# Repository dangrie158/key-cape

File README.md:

# KeyCape

a simple UI extension for your PC / Mac. 

KeyCape offers the following Hardware I/Os:

* Cherry MX Switch with LED
* Encoder with Button
* 4 general purpose LEDs

As the firmware is still in development I'm not sure yet how to implement all I/O in a good way. Probably a HID Keyboard with the Cherry Switch acting as a ESC button (so vim is usable again for the new Mac Books with touchbar) and the encoder as vol up/down.

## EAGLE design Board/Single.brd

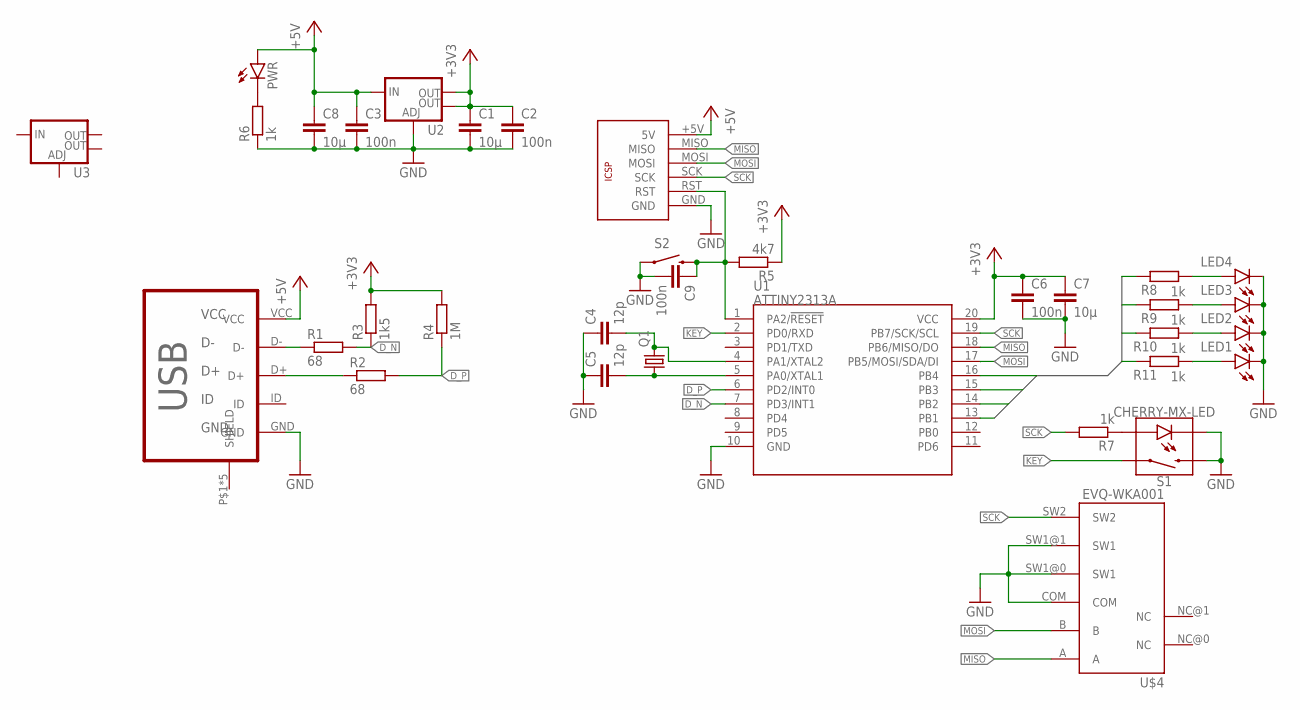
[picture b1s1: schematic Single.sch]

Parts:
C1, C7, C8: 10µ; C0603
C2, C3, C6, C9: 100n; C0603
C4, C5: 12p; C0603
LED1, LED2, LED3, LED4: LED0603; LED-0603
PWR: LED0603; LED-0603
Q1: CRYSTALCTS406; CTS406
R1, R2: 68; R0603
R3: 1k5; R0603
R4: 1M; R0603
R5: 4k7; R0603
R6, R7, R8, R9, R10, R11: 1k; R0603
S1: CHERRY-MX-LED
S2: SWITCH-MOMENTARY-2SMD-1101NE; TACTILE-SWITCH-1101NE
U1: ATTINY2313A; SOP20W
U2, U3: V_REG_LM1117SOT223; SOT223
U$1: ICSPTHROUGHHOLE; ICSP-THROUGHHOLE
U$2: MICRO-USB-B; MICRO_USB_4_LEGS
U$4: EVQ-WKA001

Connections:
+3V3: C1.1, C2.1, C6.1, C7.1, R3.2, R4.2, R5.1, U1.20 (VCC), U2.2 (OUT), U2.4 (OUT)
+5V: C3.1, C8.1, PWR.A, U2.3 (IN), U$1.+5V (5V), U$2.VCC
DUSB_N: R1.1, U$2.D-
DUSB_P: R2.1, U$2.D+
D_N: R1.2, R3.1, U1.7 (PD3/INT1)
D_P: R2.2, R4.1, U1.6 (PD2/INT0)
GND: C1.2, C2.2, C3.2, C4.1, C5.1, C6.2, C7.2, C8.2, C9.2, LED1.C, LED2.C, LED3.C, LED4.C, R6.1, S1.K (C), S1.S2, S2.1, U1.10 (GND), U2.1 (ADJ), U$1.GND, U$2.GND, U$4.COM, U$4.SW1@0 (SW1), U$4.SW1@1 (SW1)
KEY: S1.S1, U1.2 (PD0/RXD)
LED1: R11.2, U1.13 (PB1)
LED2: R10.2, U1.14 (PB2)
LED3: R9.2, U1.15 (PB3)
LED4: R8.2, U1.16 (PB4)
MISO: U1.18 (PB6/MISO/DO), U$1.MISO, U$4.A
MOSI: U1.17 (PB5/MOSI/SDA/DI), U$1.MOSI, U$4.B
unnamed: C4.2, Q1.3 (2), U1.4 (PA1/XTAL2)
unnamed: C5.2, Q1.1, U1.5 (PA0/XTAL1)
unnamed: PWR.C, R6.2
unnamed: C9.1, R5.2, S2.2, U1.1 (PA2/!RESET), U$1.RST
unnamed: R7.1, S1.A
unnamed: LED4.A, R8.1
unnamed: LED3.A, R9.1
unnamed: LED2.A, R10.1
unnamed: LED1.A, R11.1
SCK: R7.2, U1.19 (PB7/SCK/SCL), U$1.SCK, U$4.SW2

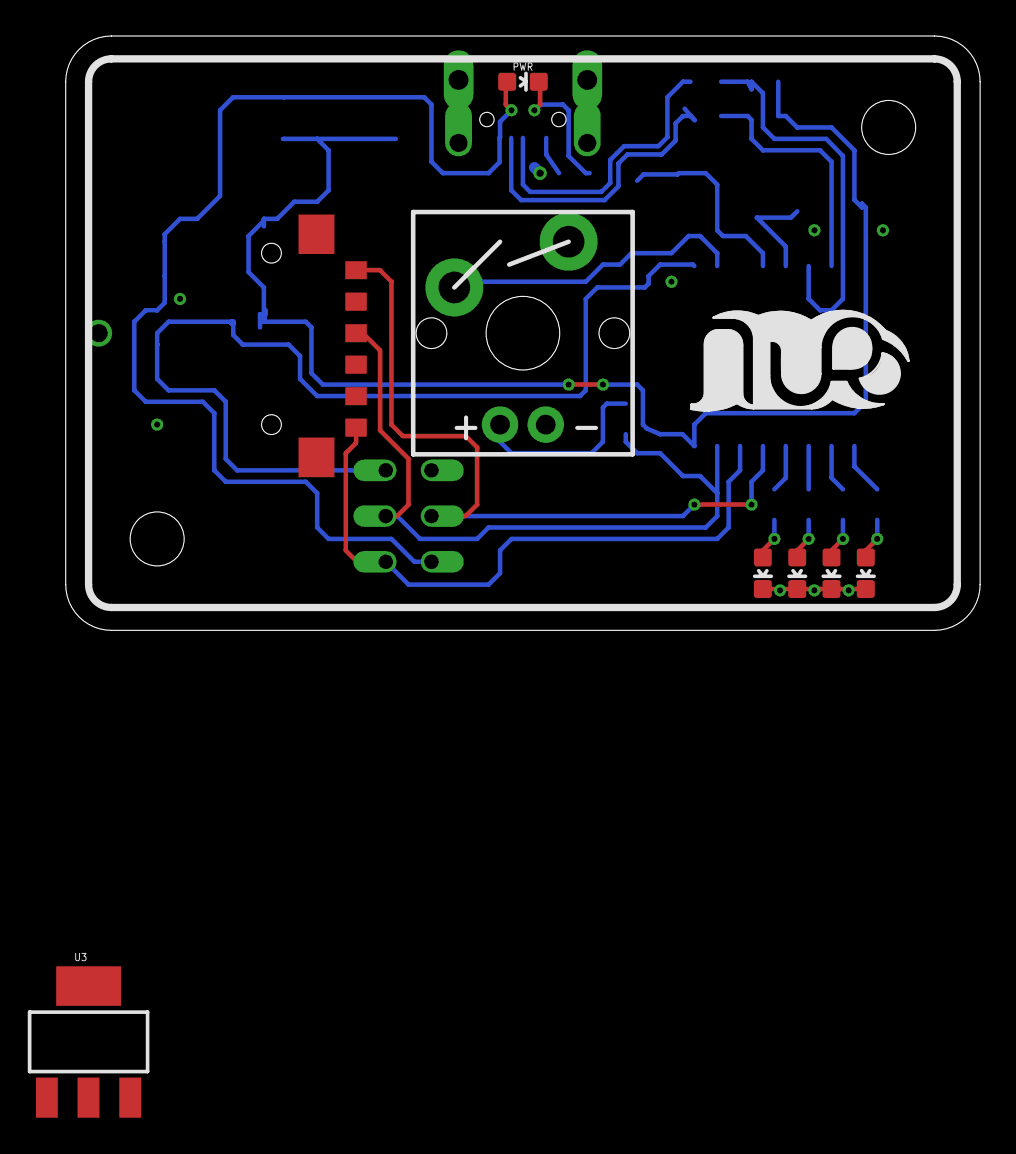
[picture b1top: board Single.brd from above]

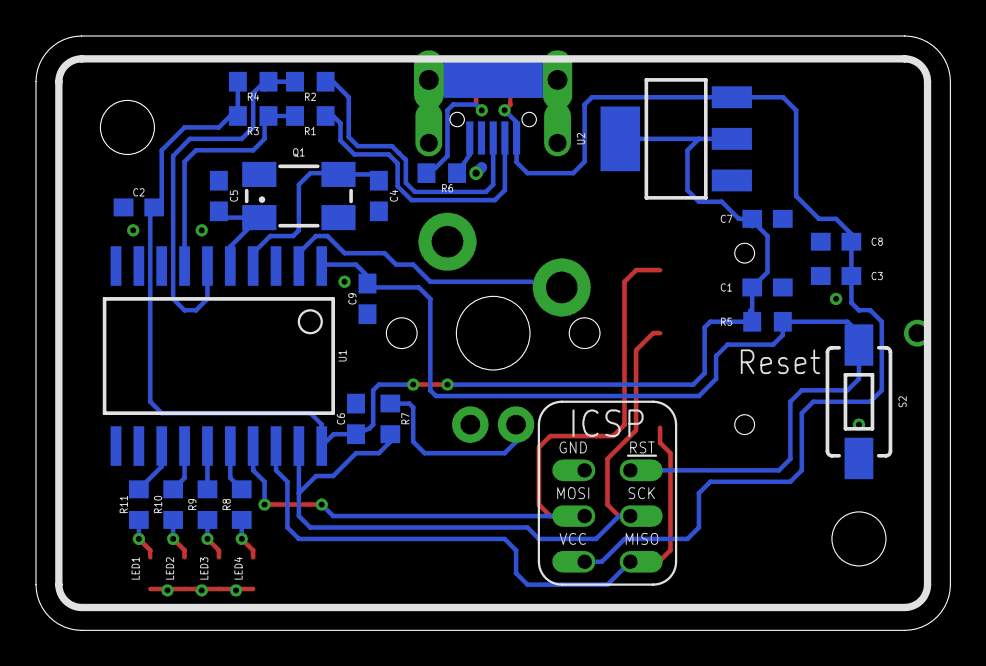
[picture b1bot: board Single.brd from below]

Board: 2 copper layers, 50.8 x 33.0 mm, 35 parts (26 on the bottom side), 24 nets.

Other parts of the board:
U$3: LOGO-SILKSCREEN

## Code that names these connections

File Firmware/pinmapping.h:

// ***********************************************************
// ***                    USB HID KEY DEFS                 ***
// *** http://www.usb.org/developers/hidpage/Hut1_12v2.pdf ***
// ***********************************************************
#define KEY_ESCAPE 0x29
#define KEY_MUTE 0x7F
#define KEY_VOL_DOWN 0x81
#define KEY_VOL_UP 0x80

// ***********************************************************
// ***                    USB HID LED DEFS                 ***
// *** http://www.usb.org/developers/hidpage/Hut1_12v2.pdf ***
// ***********************************************************
#define NUM_LOCK 0x01
#define CAPS_LOCK 0x02
#define SCROLL_LOCK 0x04

// ***********************************************************
// ***                      PIN MAPPING                    ***
// ***********************************************************
#define LED1 PB1
#define LED2 PB2
#define LED3 PB3
#define LED4 PB4
#define LED_KEY PB7
#define LED_DDR DDRB
#define LED_PORT PORTB

#define ENC_A PB6
#define ENC_B PB5
#define ENC_BTN PB7
#define ENC_DDR DDRB
#define ENC_PIN PINB
#define ENC_PORT PORTB

#define KEY PD0
#define KEY_DDR DDRD
#define KEY_PIN PIND
#define KEY_PORT PORTD

#define USB_DDR DDRD
#define USB_PORT PORTD
#define USB_PIN PIND
#define USB_P PD2
#define USB_N PD3

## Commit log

2016-12-24 added Hardware Layout
2016-12-24 added first version of firmware + build system

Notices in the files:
parts and their libraries:
SparkFun-LED: Licensing: Creative Commons ShareAlike 4.0 International - https://creativecommons.org/licenses/by-sa/4.0
